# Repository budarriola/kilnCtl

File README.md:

# kilnCtl

> **WARNING: read the [Liability waiver and safety disclaimer](#liability-waiver-and-safety-disclaimer)
> before you build, flash, wire, or power anything from this repository.**
> This is an unfinished, experimental controller for an appliance that runs above
> 1000 °C on mains power. Even where it is believed to be stable, assume it **will**
> start a fire that burns your house down with everyone inside it.

A kiln controller: three KiCad boards, two independent firmwares, and the PC
tooling that drives both.

Heating is commanded by an ESP32-S3 through solid-state relays. A separate
RP2040 watches the same kiln and can cut power through a mechanical pilot relay
that is wired in series with the contactor coil. The two processors talk over an
opto-isolated UART, and the main processor is not allowed to heat unless the
safety processor is answering.

## Start here

**[ROADMAP.md](ROADMAP.md)** is the top-level plan across both processors. It
holds the milestone order and the cross-processor dependencies, and links to the
plan that owns each area. If you do not already know which document covers what
you are about to do, start there.

## Running the regression suite

```
python tools/regression_suite.py
```

One command, every automated gate this repo has, one pass/fail summary and a
non-zero exit on any failure (usable in CI or a pre-commit hook). It runs, in
order: `tools/run_all_checks.ps1` (the mechanical `check_*.ps1` guards, plus
the JS/browser harnesses and the headless-Chrome responsive sweep, which are
themselves wired into that script's discovery); then, in parallel, the KilnFW
and SaftyFW off-target host-test suites and the `tools/PcTools` pytest suite
(its live-bench tests self-skip with no board attached); then,
in parallel, the two target firmware *compiles* (KilnFW over ESP-IDF, SaftyFW
over pico-sdk -- no flashing, ever). One gate failing does not stop the
others; the final summary lists every gate's pass/fail and points at the full
log for anything that failed. See the script's own header comment for why
each stage is grouped and parallelized the way it is.

## Opening this repository

On a fresh clone, run **[`tools/setup.ps1`](tools/setup.ps1)** first — it
discovers where ESP-IDF, clangd and OpenOCD live on this machine and generates
the config files that cannot be committed. Full detail:
[docs/SETUP.md](docs/SETUP.md).

In VS Code, open **`kilnCtl.code-workspace`** rather than the `kilnCtl` folder.
The ESP-IDF extension treats a workspace folder as one project and needs a
`CMakeLists.txt` in it; the repository root does not have one. The workspace file
lists each firmware, `tools/PcTools` and `hardware` as folders in their own right,
and carries the shared tasks.

Shell commands in this repository are written to run from the root, so they carry
a path argument: `idf.py -C firmware/KilnFW build`,
`uv run --project tools/PcTools kilnctrl-gui`.

## Layout

```
hardware/   KiCad projects, shared library, datasheets, LTspice, sourcing
firmware/   KilnFW (ESP32-S3), SaftyFW (RP2040), CommonFW (shared)
tools/      PcTools - GUI and MCP server for both processors
docs/       System-level documents that span hardware and firmware
```

`mykicadMcp/` and `pdfMcp/` both moved under `tools/` 2026-08-28.
The rationale for the split, and what broke during it, is
[docs/REPO_LAYOUT.md](docs/REPO_LAYOUT.md).

## The three boards

| Board | What it is |
|---|---|
| `hardware/mainBoard` | ESP32-S3 controller, SSR drivers, current sense, isolated link, safety RP2040 |
| `hardware/ThermocoupleBoard` | 3-channel MAX31856 daughterboard |
| `hardware/SaftyThermocoupleBoard` | The safety processor's own thermocouple front end |

`Thermocouple.kicad_sch` appears in more than one project as a copy of the same
circuit, so a fix found in one usually applies to the others.

## The two firmwares

- **`firmware/KilnFW`** — ESP-IDF. Thermocouples, PID, profile execution, Wi-Fi
  provisioning, web UI. Partly built, partly verified on hardware; the honest
  ledger is [firmware/KilnFW/docs/PROJECT_STATUS.md](firmware/KilnFW/docs/PROJECT_STATUS.md).
- **`firmware/SaftyFW`** — pico-sdk and FreeRTOS SMP. Independent overheat and
  fault detection, owns the pilot relay. Planned in detail, **not yet built**.
- **`firmware/CommonFW`** — the link contract and its codecs, implemented once
  and linked by both. Also not yet built.

The safety processor's job is to catch faults, not to be sensitive: every trip
has to clear both a magnitude that correct operation cannot reach and a duration
a transient cannot sustain. That reasoning is
[firmware/SaftyFW/docs/SAFETY_MODEL.md](firmware/SaftyFW/docs/SAFETY_MODEL.md).

## Tooling

`tools/PcTools` is one GUI and one MCP server for both processors — serial to
the ESP, the isolated UART or SWD to the Pico, per-processor consoles and log
files. See [tools/PcTools/README.md](tools/PcTools/README.md) for what exists and
[tools/PcTools/TODO.md](tools/PcTools/TODO.md) for what is planned.

`mykicadMcp` is a separate submodule exposing KiCad inspection, sourcing and
autorouting over MCP.

## Bench setup

Programming, debug and console for the RP2040 all go through a Raspberry Pi
Debug Probe: SWD to the DEBUG pads, and the probe's UART bridge on GP16/GP17.
The Pico's own USB is deliberately not used. Wiring is
[firmware/SaftyFW/docs/HARDWARE.md](firmware/SaftyFW/docs/HARDWARE.md) §7b.

## Liability waiver and safety disclaimer

**This project is a work in progress. It is not finished, not certified, and not
safe.** Everything in this repository (schematics, PCB layouts, firmware for both
processors, PC tools, documentation, release images, and any advice in issues or
discussions) is an experimental, hobbyist development effort that is still
changing daily.

**Even where a part of it is believed to be stable, it is not.** Code that has
passed every test in this repository, every bench run, and every review can still
fail in the field. Treat every release, including those marked "stable", as a
pre-release prototype.

**Assume it will burn your house down with everyone inside.** A kiln is a
resistive heater that reaches well above 1000 °C, draws tens of amps from mains
power, and is often left unattended for many hours. A controller fault, a
firmware bug, a stuck or welded relay, a failed thermocouple, a wiring mistake, a
bad update, a power glitch, or a single misread value can leave the elements
energized with nothing to stop them. The likely result is a fire that destroys the
building and kills or seriously injures the people and animals inside it.
Electrocution, burns, toxic fumes, and damage to the kiln, its contents and
nearby property are also likely. Plan as if these outcomes will happen, not as if
they might.

**The safety processor does not make this safe.** The RP2040 safety processor, its
trip guards, the E-stop path, the pilot relay, and every other protective feature
described here are part of the same unfinished, unverified design. They have not
been independently evaluated and must not be relied on to prevent fire, injury or
death. This design does not replace a certified, independent over-temperature
cutoff, a correctly rated contactor, proper overcurrent protection, a
non-combustible installation, working smoke and fire detection, and a person
physically present and watching the kiln.

**No certification.** Nothing here has been tested, listed or approved by UL, CSA,
CE, TÜV, or any other safety or standards body, and nothing here complies with
any electrical, building or fire code. Installing it may break local law, void
your insurance, and void the kiln manufacturer's warranty. Mains wiring must be
done by a licensed electrician where your jurisdiction requires it.

**No warranty.** This project is provided "AS IS" and "AS AVAILABLE", without
warranty of any kind, express or implied. That includes, without limitation, any
warranty of merchantability, fitness for a particular purpose, safety, accuracy,
reliability, non-infringement, or that it will work at all.

**No liability.** To the fullest extent permitted by law, the authors,
contributors, copyright holders, and anyone who distributes this project are not
liable for any claim, damage, injury, death, loss of property, loss of data, loss
of income, or other loss of any kind, whether direct, indirect, incidental,
special, consequential, or punitive, and whether based on contract, tort
(including negligence), strict liability, or any other theory. This holds even if
they were told such loss was possible, and it applies to any use of this project,
any inability to use it, and any failure of it.

**You accept all risk.** By building, flashing, installing, operating, modifying,
or distributing anything from this repository, you agree that you do so entirely
at your own risk, that you are solely responsible for the safety of your
installation and of everyone and everything near it, and that you will indemnify
and hold harmless the authors and contributors against any claim arising from
your use. If you do not accept these terms, do not use this project.

**Not advice.** Nothing in this repository is professional, electrical,
engineering, or legal advice. If any part of this waiver cannot be enforced where
you live, the rest of it still applies.

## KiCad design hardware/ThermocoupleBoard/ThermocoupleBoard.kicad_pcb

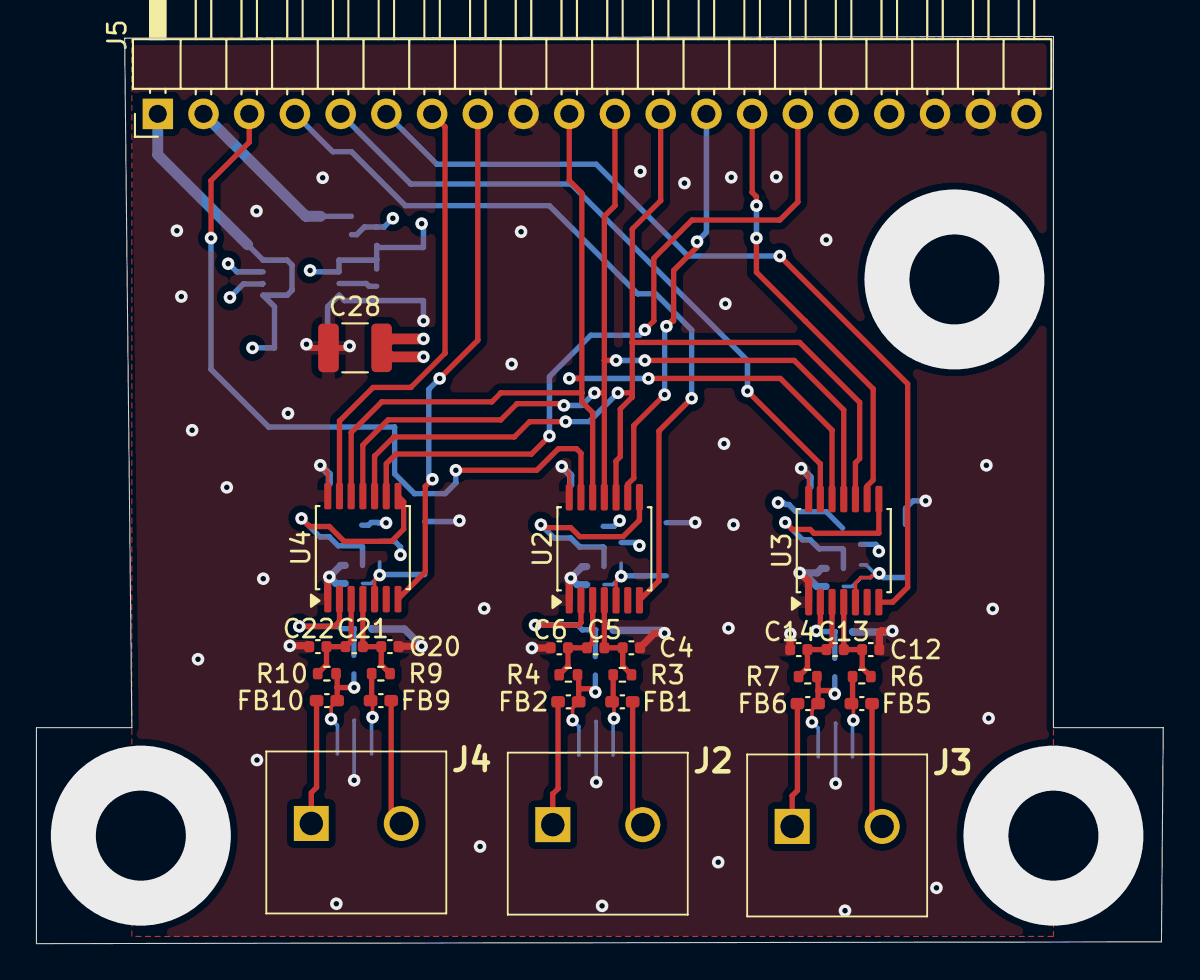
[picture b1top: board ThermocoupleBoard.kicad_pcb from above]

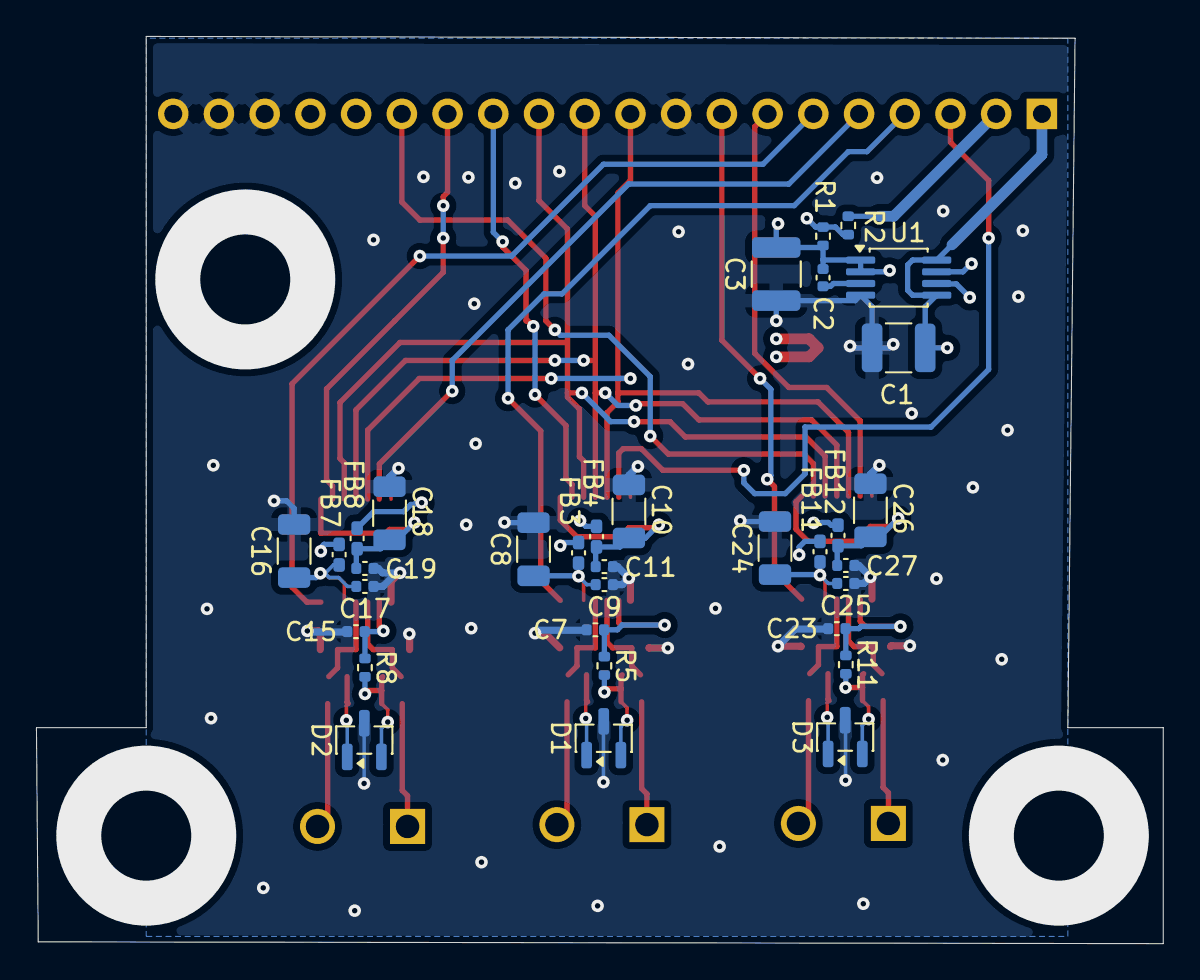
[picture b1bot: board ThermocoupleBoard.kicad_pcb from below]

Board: 4 copper layers, 62.6 x 50.4 mm, 62 parts (33 on the bottom side), 45 nets.

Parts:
C1, C3, C28: 47uF 16V; C_1210_3225Metric
C2, C4, C6, C7, C12, C14, C15, C20, C22, C23: 0.01uf; C_0402_1005Metric
C5, C9, C11, C13, C17, C19, C21, C25, C27: 0.1uf; C_0402_1005Metric
C8, C10, C16, C18, C24, C26: 2.2uF; C_1206_3216Metric
D1, D2, D3: NUP2105L; SOT-23
FB1, FB2, FB3, FB4, FB5, FB6, FB7, FB8, FB9, FB10, FB11, FB12: 1.8k; L_0402_1005Metric_Pad0.77x0.64mm_HandSolder
J2, J3, J4: 1935161
J5: Conn_01x20_Pin; PinHeader_1x20_P2.54mm_Horizontal
R1, R2: 0; R_0402_1005Metric
R3, R4, R5, R6, R7, R8, R9, R10, R11: 2.2k; R_0402_1005Metric
U1: LT1962-3.3; MSOP-8_3x3mm_P0.65mm
U2, U3, U4: MAX31856; TSSOP-14_4.4x5mm_P0.65mm

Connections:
3.3V_A: C2.1, C3.2, FB3.2, FB7.2, FB11.2, R1.2, U1.1 (OUT), U1.2 (SENSE)
3.3_D: C28.2, FB4.2, FB8.2, FB12.2, R1.1, R2.1
5V: C1.2, J5.1, U1.5 (~SHDN), U1.8 (IN)
/CLK: J5.12, U2.10 (SCK), U3.10 (SCK), U4.10 (SCK)
/CS0: J5.13, U2.9 (~CS)
/CS1: J5.14, U3.9 (~CS)
/CS2: J5.15, U4.9 (~CS)
/MISO: J5.11, U2.11 (SDO), U3.11 (SDO), U4.11 (SDO)
/MOSI: J5.10, U2.12 (SDI), U3.12 (SDI), U4.12 (SDI)
/thermoDrdy_0: J5.4, U2.7 (~DRDY)
/thermoDrdy_1: J5.6, U3.7 (~DRDY)
/thermoDrdy_2: J5.8, U4.7 (~DRDY)
/thermoFault_0: J5.3, U2.13 (~FAULT)
/thermoFault_1: J5.5, U3.13 (~FAULT)
/thermoFault_2: J5.7, U4.13 (~FAULT)
GND: C1.1, C3.1, C4.1, C6.2, C7.2, C8.2, C9.2, C10.2, C11.2, C12.1, C14.2, C15.2, C16.2, C17.2, C18.2, C19.2, C20.1, C22.2, C23.2, C24.2, C25.2, C26.2, C27.2, C28.1, D1.3 (A), D2.3 (A), D3.3 (A), J5.9, J5.18, J5.19, J5.20, U1.4 (GND), U2.1 (AGND), U2.14 (DGND), U3.1 (AGND), U3.14 (DGND), U4.1 (AGND), U4.14 (DGND)
unnamed: D1.1 (K), FB1.2, R3.2
unnamed: D1.2 (K), FB2.2, R4.2, R5.2
unnamed: D2.1 (K), FB5.2, R6.2
unnamed: D2.2 (K), FB6.2, R7.2, R8.2
unnamed: D3.1 (K), FB9.2, R9.2
unnamed: D3.2 (K), FB10.2, R10.2, R11.2
unnamed: FB1.1, J2.2
unnamed: FB2.1, J2.1
unnamed: FB5.1, J3.2
unnamed: FB6.1, J3.1
unnamed: FB9.1, J4.2
unnamed: FB10.1, J4.1
unnamed: J5.2, R2.2
unnamed: C2.2, U1.3 (BYP)
unnamed: C8.1, C9.1, FB3.1, U2.5 (AVDD)
unnamed: C7.1, R5.1, U2.2 (BIAS)
unnamed: C10.1, C11.1, FB4.1, U2.8 (DVDD)
unnamed: C4.2, C5.1, R3.1, U2.4 (T+)
unnamed: C5.2, C6.1, R4.1, U2.3 (T-)
unnamed: C16.1, C17.1, FB7.1, U3.5 (AVDD)
unnamed: C15.1, R8.1, U3.2 (BIAS)
unnamed: C18.1, C19.1, FB8.1, U3.8 (DVDD)
unnamed: C12.2, C13.1, R6.1, U3.4 (T+)
unnamed: C13.2, C14.1, R7.1, U3.3 (T-)
unnamed: C24.1, C25.1, FB11.1, U4.5 (AVDD)
unnamed: C23.1, R11.1, U4.2 (BIAS)
unnamed: C26.1, C27.1, FB12.1, U4.8 (DVDD)
unnamed: C20.2, C21.1, R9.1, U4.4 (T+)
unnamed: C21.2, C22.1, R10.1, U4.3 (T-)

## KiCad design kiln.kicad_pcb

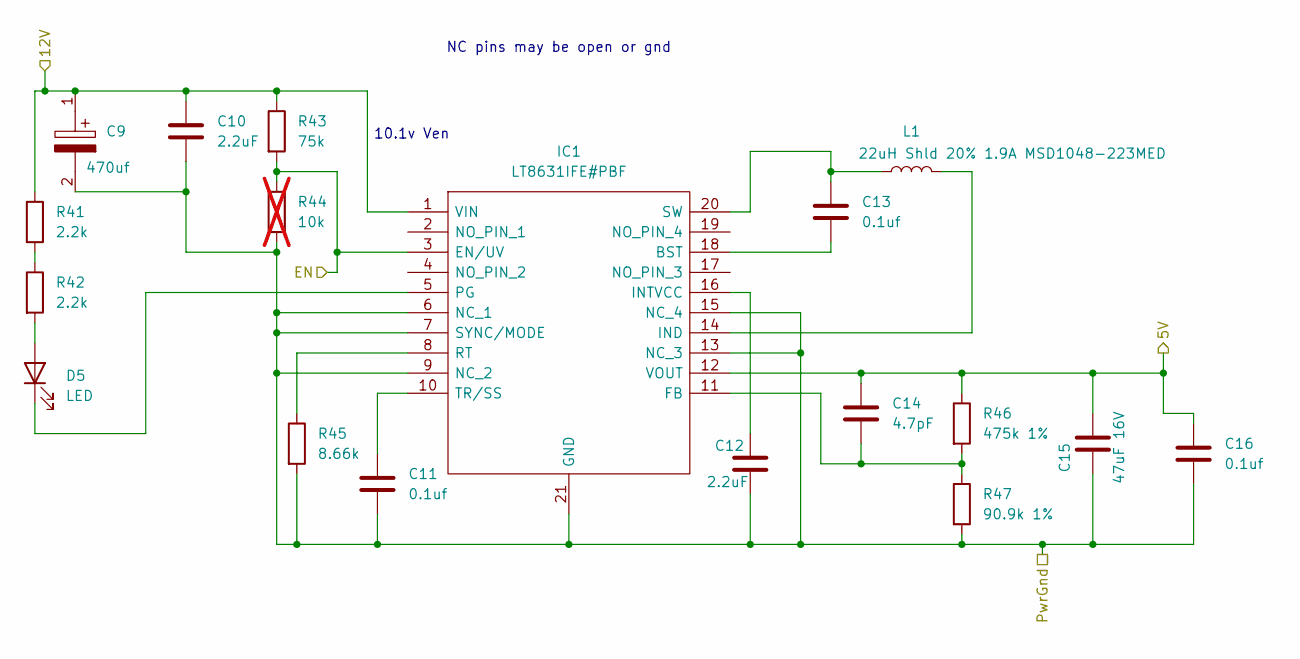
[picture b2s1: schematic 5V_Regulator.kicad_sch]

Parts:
C9: 470uf; CAPAE1360X1450N; Mouser Part Number 647-UCM1H471MNJ1MS
C10, C12: 2.2uF; C_1206_3216Metric
C11, C13, C16: 0.1uf; C_0402_1005Metric
C14: 4.7pF; C_0402_1005Metric
C15: 47uF 16V; C_1210_3225Metric
D5: LED; LED_0402_1005Metric
IC1: LT8631IFE#PBF; SOP65P640X120-21N; Mouser Part Number 584-LT8631IFE#PBF
L1: 22uH Shld 20% 1.9A MSD1048-223MED; L_Bourns_SRP1038C_10.0x10.0mm
R41, R42: 2.2k; R_0805_2012Metric
R43: 75k; R_0402_1005Metric
R44: 10k; R_0402_1005Metric; not fitted
R45: 8.66k; R_0402_1005Metric
R46: 475k 1%; R_0402_1005Metric
R47: 90.9k 1%; R_0402_1005Metric

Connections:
5V_Main: C14.1, C15.2, C16.1, IC1.12 (VOUT), R46.1; also elsewhere on the board
12V_Main: C9.1, C10.1, IC1.1 (VIN), R41.1, R43.1; also elsewhere on the board
/MainRegulator/PGoodMain: IC1.3 (EN/UV), R43.2, R44.1; also elsewhere on the board
GND_Main: C9.2, C10.2, C11.2, C12.2, C15.1, C16.2, IC1.6 (NC_1), IC1.7 (SYNC/MODE), IC1.9 (NC_2), IC1.13 (NC_3), IC1.15 (NC_4), IC1.21 (GND), R44.2, R45.2, R47.2; also elsewhere on the board
unnamed: D5.2 (A), R42.2
unnamed: D5.1 (K), IC1.5 (PG)
unnamed: C13.2, IC1.18 (BST)
unnamed: C14.2, IC1.11 (FB), R46.2, R47.1
unnamed: IC1.14 (IND), L1.2
unnamed: C12.1, IC1.16 (INTVCC)
unnamed: IC1.8 (RT), R45.1
unnamed: C13.1, IC1.20 (SW), L1.1
unnamed: C11.1, IC1.10 (TR/SS)
unnamed: R41.2, R42.1

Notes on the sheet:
10.1v Ven
NC pins may be open or gnd

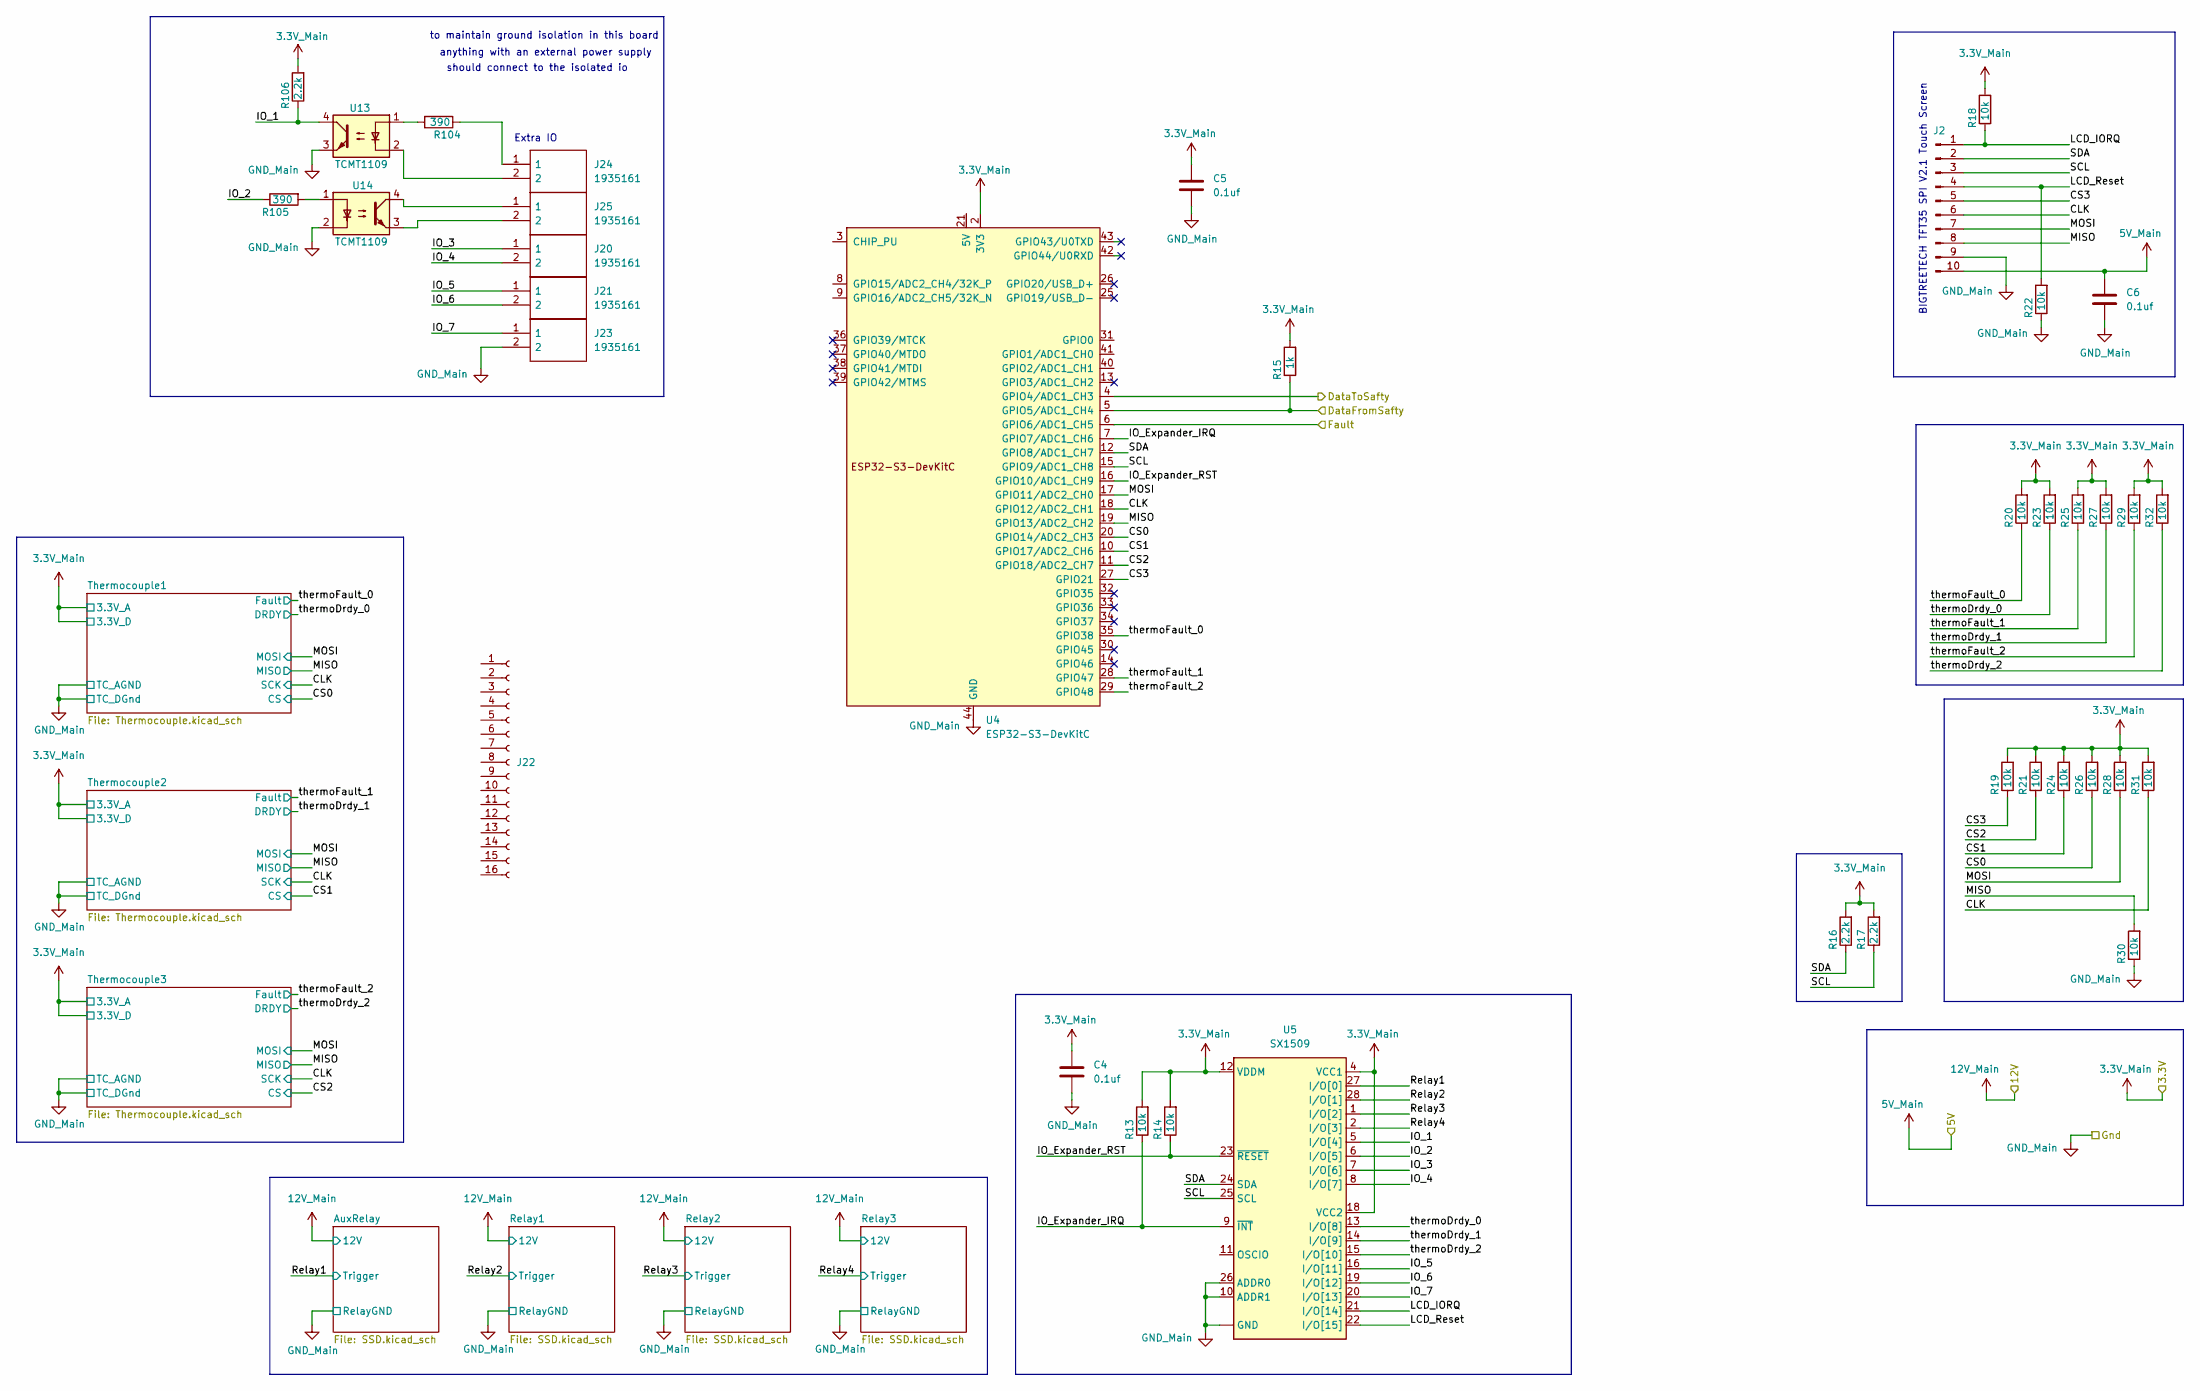
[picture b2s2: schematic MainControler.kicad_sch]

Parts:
C4, C5, C6: 0.1uf; C_0402_1005Metric
J2: Conn_01x10_Pin; JST_XH_B10B-XH-AM_1x10_P2.50mm_Vertical
J20, J21, J23, J24, J25: 1935161; Mouser Part Number 651-1935161
J22: Conn_01x16_Socket; PinSocket_1x16_P2.54mm_Horizontal
R13, R14, R18, R19, R20, R21, R22, R23, R24, R25, R26, R27, R28, R29, R30, R31, R32: 10k; R_0402_1005Metric
R15: 1k; R_0402_1005Metric
R16, R17, R106: 2.2k; R_0402_1005Metric
R104, R105: 390; R_0402_1005Metric
U4: ESP32-S3-DevKitC
U5: SX1509; QFN-28-1EP_4x4mm_P0.4mm_EP2.6x2.6mm; Manufacturer_Part_Number SX1509BIULTRT
U13, U14: TCMT1109; SOP-4_4.4x2.6mm_P1.27mm

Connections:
3.3V_Main: C4.1, C5.1, R13.2, R14.2, R15.2, R16.2, R17.2, R18.2, R19.2, R20.2, R21.2, R23.2, R24.2, R25.2, R26.2, R27.2, R28.2, R29.2, R31.2, R32.2, R106.2, U4.1 (3V3), U4.2 (3V3), U5.4 (VCC1), U5.12 (VDDM), U5.18 (VCC2); also elsewhere on the board
5V_Main: C6.1, J2.10; also elsewhere on the board
/MainControler/CLK: J2.6, R31.1, U4.18 (GPIO12/ADC2_CH1); also elsewhere on the board
/MainControler/CS0: R26.1, U4.20 (GPIO14/ADC2_CH3); also elsewhere on the board
/MainControler/CS1: R24.1, U4.10 (GPIO17/ADC2_CH6); also elsewhere on the board
/MainControler/CS2: R21.1, U4.11 (GPIO18/ADC2_CH7); also elsewhere on the board
/MainControler/CS3: J2.5, R19.1, U4.27 (GPIO21)
/MainControler/DataFromSafty: R15.1, U4.5 (GPIO5/ADC1_CH4); also elsewhere on the board
/MainControler/DataToSafty: U4.4 (GPIO4/ADC1_CH3); also elsewhere on the board
/MainControler/Fault: U4.6 (GPIO6/ADC1_CH5); also elsewhere on the board
/MainControler/IO_1: R106.1, U5.5 (I/O[4]), U13.4
/MainControler/IO_2: R105.1, U5.6 (I/O[5])
/MainControler/IO_3: J20.1, U5.7 (I/O[6])
/MainControler/IO_4: J20.2, U5.8 (I/O[7])
/MainControler/IO_5: J21.1, U5.16 (I/O[11])
/MainControler/IO_6: J21.2, U5.19 (I/O[12])
/MainControler/IO_7: J23.1, U5.20 (I/O[13])
/MainControler/IO_Expander_IRQ: R13.1, U4.7 (GPIO7/ADC1_CH6), U5.9 (~INT)
/MainControler/IO_Expander_RST: R14.1, U4.16 (GPIO10/ADC1_CH9), U5.23 (~RESET)
/MainControler/LCD_IORQ: J2.1, R18.1, U5.21 (I/O[14])
/MainControler/LCD_Reset: J2.4, R22.2, U5.22 (I/O[15])
/MainControler/MISO: J2.8, R30.2, U4.19 (GPIO13/ADC2_CH2); also elsewhere on the board
/MainControler/MOSI: J2.7, R28.1, U4.17 (GPIO11/ADC2_CH0); also elsewhere on the board
/MainControler/Relay1: U5.27 (I/O[0]); also elsewhere on the board
/MainControler/Relay2: U5.28 (I/O[1]); also elsewhere on the board
/MainControler/Relay3: U5.1 (I/O[2]); also elsewhere on the board
/MainControler/Relay4: U5.2 (I/O[3]); also elsewhere on the board
/MainControler/SCL: J2.3, R17.1, U4.15 (GPIO9/ADC1_CH8), U5.25 (SCL)
/MainControler/SDA: J2.2, R16.1, U4.12 (GPIO8/ADC1_CH7), U5.24 (SDA)
/MainControler/thermoDrdy_0: R23.1, U5.13 (I/O[8]); also elsewhere on the board
/MainControler/thermoDrdy_1: R27.1, U5.14 (I/O[9]); also elsewhere on the board
/MainControler/thermoDrdy_2: R32.1, U5.15 (I/O[10]); also elsewhere on the board
/MainControler/thermoFault_0: R20.1, U4.35 (GPIO38); also elsewhere on the board
/MainControler/thermoFault_1: R25.1, U4.28 (GPIO47); also elsewhere on the board
/MainControler/thermoFault_2: R29.1, U4.29 (GPIO48); also elsewhere on the board
GND_Main: C4.2, C5.2, C6.2, J2.9, J23.2, R22.1, R30.1, U4.22 (GND), U4.23 (GND), U4.24 (GND), U4.44 (GND), U5.3 (GND), U5.10 (ADDR1), U5.17 (GND), U5.26 (ADDR0), U5.29 (GND), U13.3, U14.2; also elsewhere on the board
unnamed: J24.1, R104.1
unnamed: J24.2, U13.2
unnamed: J25.1, U14.4
unnamed: J25.2, U14.3
unnamed: R104.2, U13.1
unnamed: R105.2, U14.1

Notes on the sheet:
BIGTREETECH TFT35 SPI V2.1 Touch Screen
anything with an external power supply
to maintain ground isolation in this board
should connect to the isolated io
Extra IO

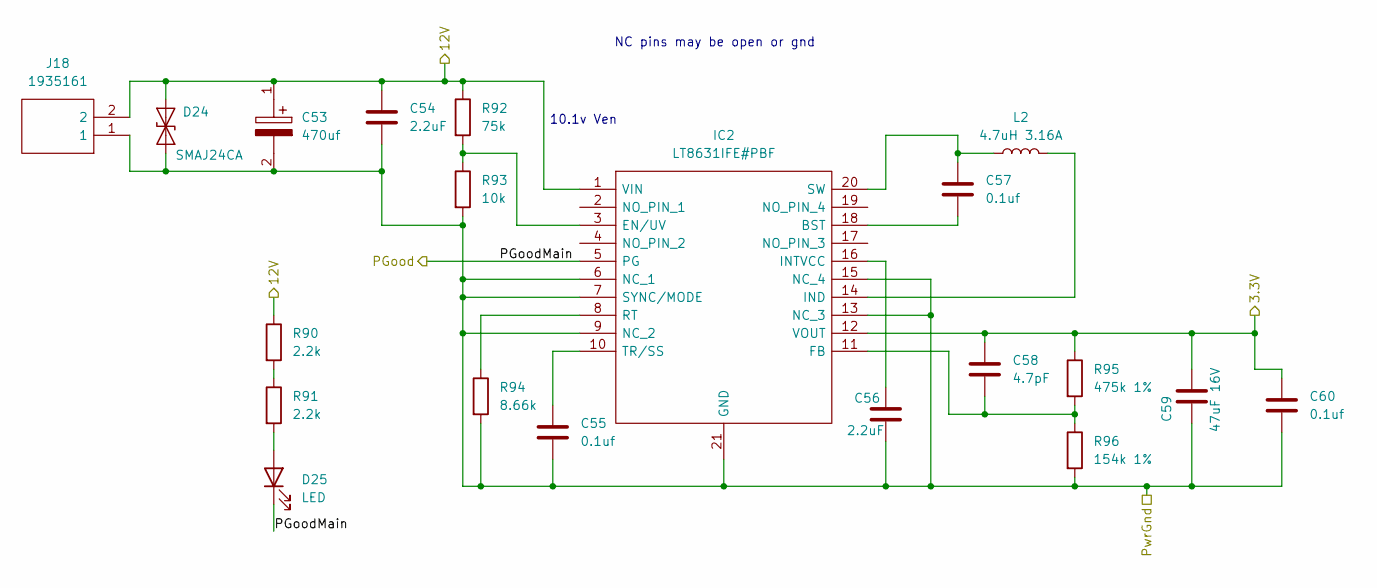
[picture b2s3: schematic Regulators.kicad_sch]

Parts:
C53: 470uf; CAPAE1360X1450N; Mouser Part Number 647-UCM1H471MNJ1MS
C54, C56: 2.2uF; C_1206_3216Metric
C55, C57, C60: 0.1uf; C_0402_1005Metric
C58: 4.7pF; C_0402_1005Metric
C59: 47uF 16V; C_1210_3225Metric
D24: SMAJ24CA; D_SMA
D25: LED; LED_0402_1005Metric
IC2: LT8631IFE#PBF; SOP65P640X120-21N; Mouser Part Number 584-LT8631IFE#PBF
J18: 1935161; Mouser Part Number 651-1935161
L2: 4.7uH 3.16A; L_7.3x7.3_H4.5
R90, R91: 2.2k; R_0805_2012Metric
R92: 75k; R_0402_1005Metric
R93: 10k; R_0402_1005Metric
R94: 8.66k; R_0402_1005Metric
R95: 475k 1%; R_0402_1005Metric
R96: 154k 1%; R_0402_1005Metric

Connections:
3.3V_Main: C58.1, C59.2, C60.1, IC2.12 (VOUT), R95.1; also elsewhere on the board
12V_Main: C53.1, C54.1, D24.2 (A2), IC2.1 (VIN), J18.2, R90.1, R92.1; also elsewhere on the board
/MainRegulator/PGoodMain: D25.1 (K), IC2.5 (PG); also elsewhere on the board
GND_Main: C53.2, C54.2, C55.2, C56.2, C59.1, C60.2, D24.1 (A1), IC2.6 (NC_1), IC2.7 (SYNC/MODE), IC2.9 (NC_2), IC2.13 (NC_3), IC2.15 (NC_4), IC2.21 (GND), J18.1, R93.2, R94.2, R96.2; also elsewhere on the board
unnamed: D25.2 (A), R91.2
unnamed: C57.2, IC2.18 (BST)
unnamed: IC2.3 (EN/UV), R92.2, R93.1
unnamed: C58.2, IC2.11 (FB), R95.2, R96.1
unnamed: IC2.14 (IND), L2.2
unnamed: C56.1, IC2.16 (INTVCC)
unnamed: IC2.8 (RT), R94.1
unnamed: C57.1, IC2.20 (SW), L2.1
unnamed: C55.1, IC2.10 (TR/SS)
unnamed: R90.2, R91.1

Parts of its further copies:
C61: 470uf; CAPAE1360X1450N; Mouser Part Number 647-UCM1H471MNJ1MS
C62, C64: 2.2uF; C_1206_3216Metric
C63, C65, C68: 0.1uf; C_0402_1005Metric
C66: 4.7pF; C_0402_1005Metric
C67: 47uF 16V; C_1210_3225Metric
D26: SMAJ24CA; D_SMA
D27: LED; LED_0402_1005Metric
IC3: LT8631IFE#PBF; SOP65P640X120-21N; Mouser Part Number 584-LT8631IFE#PBF
J19: 1935161; Mouser Part Number 651-1935161
L3: 4.7uH 3.16A; L_7.3x7.3_H4.5
R97, R98: 2.2k; R_0805_2012Metric
R99: 75k; R_0402_1005Metric
R100: 10k; R_0402_1005Metric
R101: 8.66k; R_0402_1005Metric
R102: 475k 1%; R_0402_1005Metric
R103: 154k 1%; R_0402_1005Metric

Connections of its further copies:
3.3v_Safty: C66.1, C67.2, C68.1, IC3.12 (VOUT), R102.1; also elsewhere on the board
12v_Safty: C61.1, C62.1, D26.2 (A2), IC3.1 (VIN), J19.2, R97.1, R99.1; also elsewhere on the board
/SaftyRegulator/PGoodMain: D27.1 (K), IC3.5 (PG)
GND_Safty: C61.2, C62.2, C63.2, C64.2, C67.1, C68.2, D26.1 (A1), IC3.6 (NC_1), IC3.7 (SYNC/MODE), IC3.9 (NC_2), IC3.13 (NC_3), IC3.15 (NC_4), IC3.21 (GND), J19.1, R100.2, R101.2, R103.2; also elsewhere on the board
unnamed: D27.2 (A), R98.2
unnamed: C65.2, IC3.18 (BST)
unnamed: IC3.3 (EN/UV), R99.2, R100.1
unnamed: C66.2, IC3.11 (FB), R102.2, R103.1
unnamed: IC3.14 (IND), L3.2
unnamed: C64.1, IC3.16 (INTVCC)
unnamed: IC3.8 (RT), R101.1
unnamed: C65.1, IC3.20 (SW), L3.1
unnamed: C63.1, IC3.10 (TR/SS)
unnamed: R97.2, R98.1

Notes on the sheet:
NC pins may be open or gnd
10.1v Ven

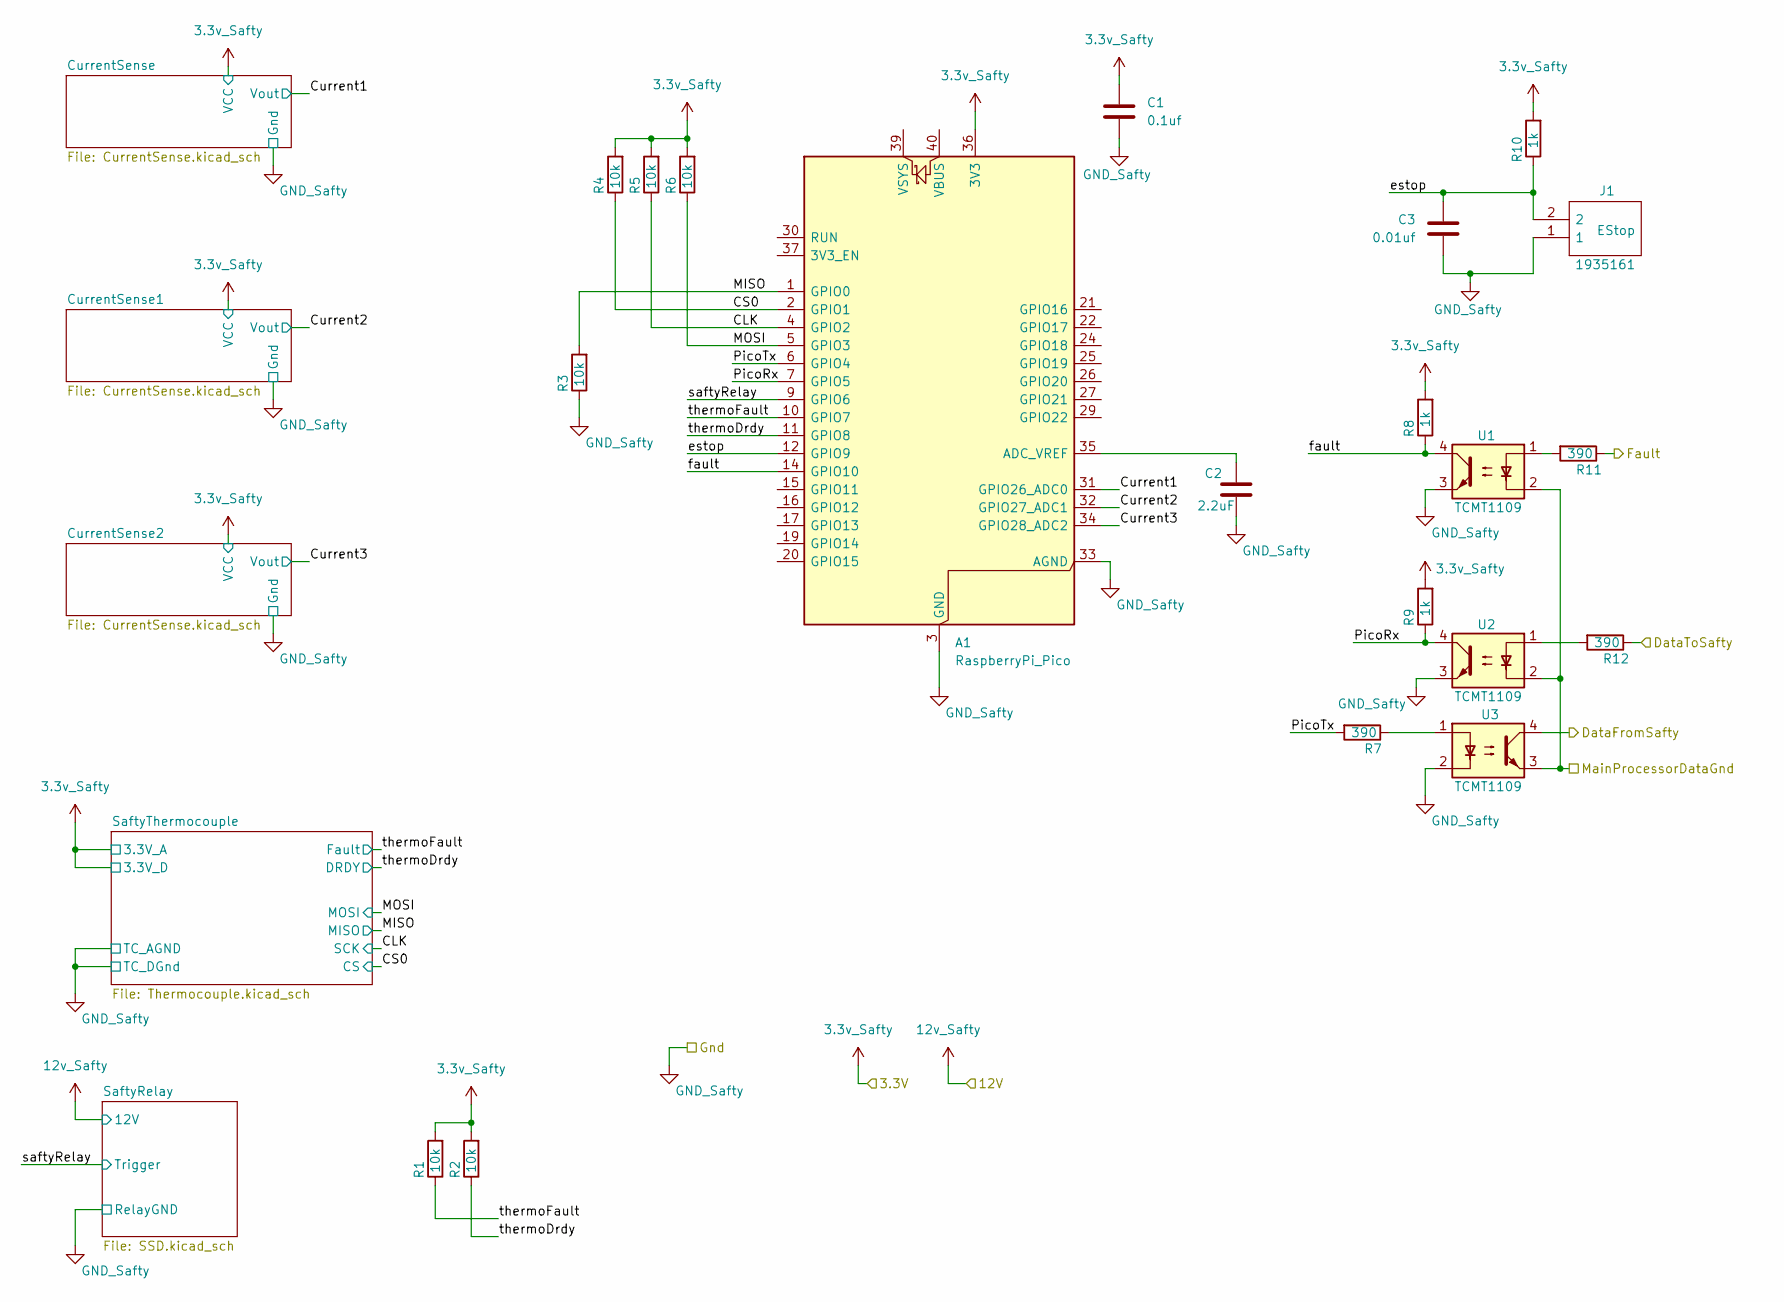
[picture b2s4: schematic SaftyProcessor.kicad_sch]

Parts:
A1: RaspberryPi_Pico; RaspberryPi_Pico_Common_Unspecified
C1: 0.1uf; C_0402_1005Metric
C2: 2.2uF; C_1206_3216Metric
C3: 0.01uf; C_0402_1005Metric
J1: 1935161; Mouser Part Number 651-1935161
R1, R2, R3, R4, R5, R6: 10k; R_0402_1005Metric
R7, R11, R12: 390; R_0402_1005Metric
R8, R9, R10: 1k; R_0402_1005Metric
U1, U2, U3: TCMT1109; SOP-4_4.4x2.6mm_P1.27mm

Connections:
3.3v_Safty: A1.36 (3V3), C1.1, R1.2, R2.2, R4.2, R5.2, R6.2, R8.2, R9.2, R10.2; also elsewhere on the board
/MainControler/DataFromSafty: R12.1; also elsewhere on the board
/MainControler/DataToSafty: U3.4; also elsewhere on the board
/MainControler/Fault: R11.1; also elsewhere on the board
/SaftyProcessor/CLK: A1.4 (GPIO2), R5.1; also elsewhere on the board
/SaftyProcessor/CS0: A1.2 (GPIO1), R4.1; also elsewhere on the board
/SaftyProcessor/Current1: A1.31 (GPIO26_ADC0); also elsewhere on the board
/SaftyProcessor/Current2: A1.32 (GPIO27_ADC1); also elsewhere on the board
/SaftyProcessor/Current3: A1.34 (GPIO28_ADC2); also elsewhere on the board
/SaftyProcessor/MISO: A1.1 (GPIO0), R3.2; also elsewhere on the board
/SaftyProcessor/MOSI: A1.5 (GPIO3), R6.1; also elsewhere on the board
/SaftyProcessor/PicoRx: A1.7 (GPIO5), R9.1, U2.4
/SaftyProcessor/PicoTx: A1.6 (GPIO4), R7.2
/SaftyProcessor/estop: A1.12 (GPIO9), C3.1, J1.2, R10.1
/SaftyProcessor/fault: A1.14 (GPIO10), R8.1, U1.4
/SaftyProcessor/saftyRelay: A1.9 (GPIO6); also elsewhere on the board
/SaftyProcessor/thermoDrdy: A1.11 (GPIO8), R2.1; also elsewhere on the board
/SaftyProcessor/thermoFault: A1.10 (GPIO7), R1.1; also elsewhere on the board
GND_Main: U1.2, U2.2, U3.3; also elsewhere on the board
GND_Safty: A1.3 (GND), A1.8 (GND), A1.13 (GND), A1.18 (GND), A1.23 (GND), A1.28 (GND), A1.33 (AGND), A1.38 (GND), C1.2, C2.2, C3.2, J1.1, R3.1, U1.3, U2.3, U3.2; also elsewhere on the board
unnamed: A1.35 (ADC_VREF), C2.1
unnamed: R7.1, U3.1
unnamed: R11.2, U1.1
unnamed: R12.2, U2.1

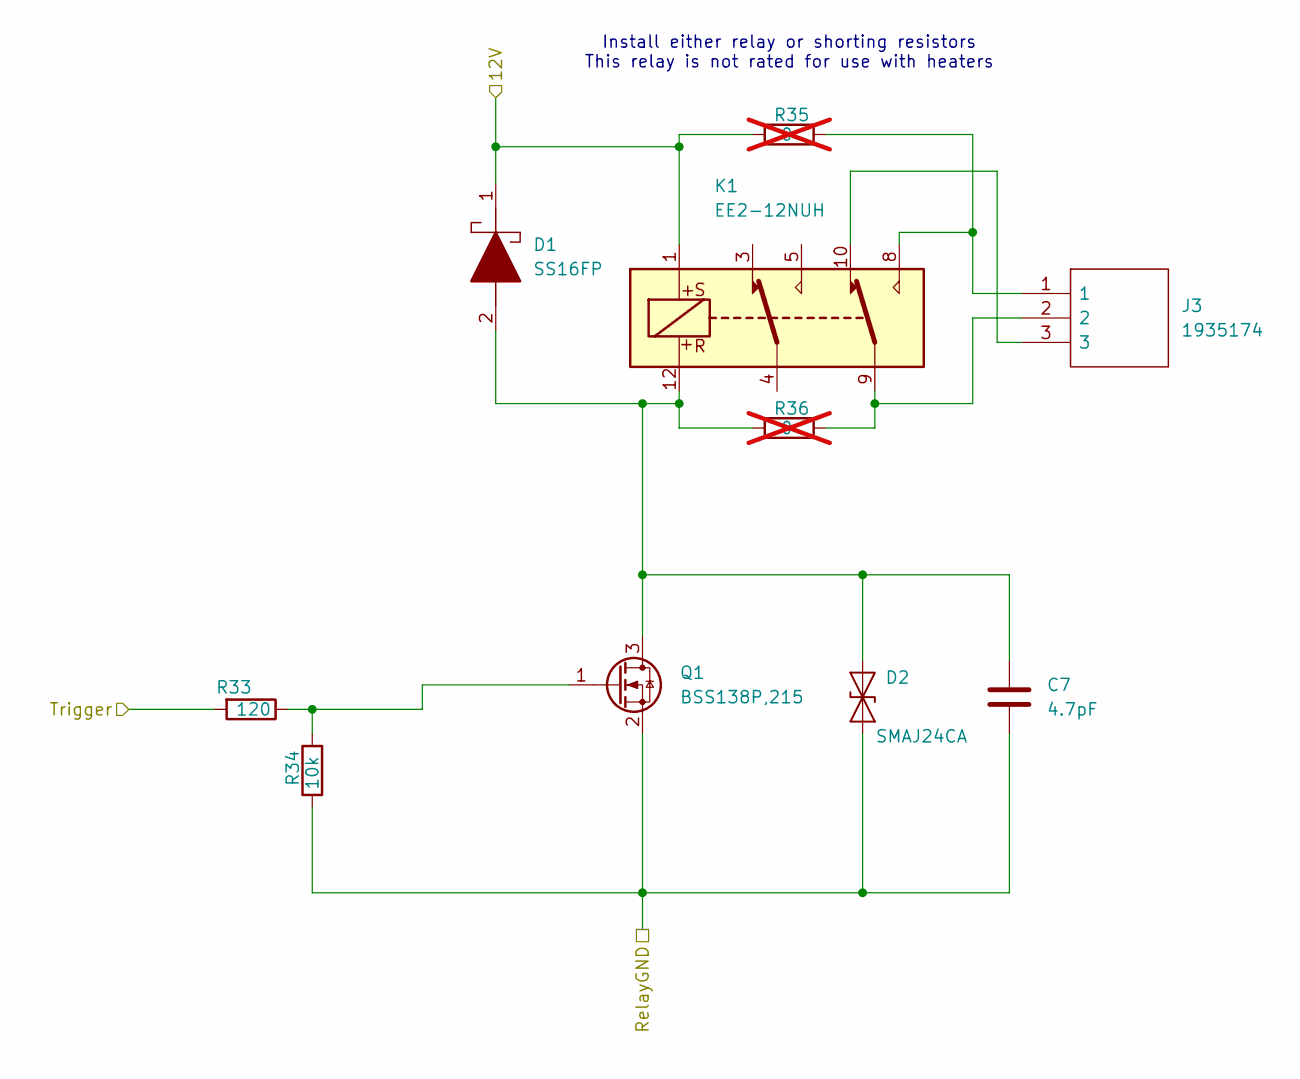
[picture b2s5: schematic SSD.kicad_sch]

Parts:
C7: 4.7pF; C_0402_1005Metric
D1: SS16FP; SS12FP; Mouser Part Number 512-SS16FP
D2: SMAJ24CA; D_SMA
J3: 1935174; Mouser Part Number 651-1935174
K1: EE2-12NUH; Relay_DPDT_Kemet_EE2_NUH
Q1: BSS138P,215; SOT-23
R33: 120; R_0402_1005Metric
R34: 10k; R_0402_1005Metric
R35, R36: 0; R_1206_3216Metric; not fitted

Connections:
12V_Main: D1.1, K1.1, R35.1; also elsewhere on the board
/MainControler/Relay2: R33.2; also elsewhere on the board
GND_Main: C7.2, D2.1 (A1), Q1.2 (S), R34.1; also elsewhere on the board
unnamed: C7.1, D1.2, D2.2 (A2), K1.12, Q1.3 (D), R36.1
unnamed: J3.1, K1.8, R35.2
unnamed: J3.2, K1.9, R36.2
unnamed: J3.3, K1.10
unnamed: Q1.1 (G), R33.1, R34.2

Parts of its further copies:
C8, C35, C42, C43: 4.7pF; C_0402_1005Metric
D3, D6, D8, D10: SS16FP; SS12FP; Mouser Part Number 512-SS16FP
D4, D7, D9, D11: SMAJ24CA; D_SMA
J4, J8, J10, J11: 1935174; Mouser Part Number 651-1935174
K2, K3, K4, K5: EE2-12NUH; Relay_DPDT_Kemet_EE2_NUH
Q2, Q3, Q4, Q5: BSS138P,215; SOT-23
R37, R57, R64, R68: 120; R_0402_1005Metric
R38, R58, R65, R69: 10k; R_0402_1005Metric
R39, R40, R59, R60, R66, R67, R70, R71: 0; R_1206_3216Metric; not fitted

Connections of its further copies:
12V_Main: D3.1, D6.1, D10.1, K2.1, K3.1, K5.1, R39.1, R59.1, R70.1; also elsewhere on the board
12v_Safty: D8.1, K4.1, R66.1; also elsewhere on the board
/MainControler/Relay1: R57.2; also elsewhere on the board
/MainControler/Relay3: R37.2; also elsewhere on the board
/MainControler/Relay4: R68.2; also elsewhere on the board
/SaftyProcessor/saftyRelay: R64.2; also elsewhere on the board
GND_Main: C8.2, C35.2, C43.2, D4.1 (A1), D7.1 (A1), D11.1 (A1), Q2.2 (S), Q3.2 (S), Q5.2 (S), R38.1, R58.1, R69.1; also elsewhere on the board
GND_Safty: C42.2, D9.1 (A1), Q4.2 (S), R65.1; also elsewhere on the board
unnamed: C8.1, D3.2, D4.2 (A2), K2.12, Q2.3 (D), R40.1
unnamed: C35.1, D6.2, D7.2 (A2), K3.12, Q3.3 (D), R60.1
unnamed: C42.1, D8.2, D9.2 (A2), K4.12, Q4.3 (D), R67.1
unnamed: C43.1, D10.2, D11.2 (A2), K5.12, Q5.3 (D), R71.1
unnamed: J4.1, K2.8, R39.2
unnamed: J4.2, K2.9, R40.2
unnamed: J4.3, K2.10
unnamed: J8.1, K3.8, R59.2
unnamed: J8.2, K3.9, R60.2
unnamed: J8.3, K3.10
unnamed: J10.1, K4.8, R66.2
unnamed: J10.2, K4.9, R67.2
unnamed: J10.3, K4.10
unnamed: J11.1, K5.8, R70.2
unnamed: J11.2, K5.9, R71.2
unnamed: J11.3, K5.10
unnamed: Q2.1 (G), R37.1, R38.2
unnamed: Q3.1 (G), R57.1, R58.2
unnamed: Q4.1 (G), R64.1, R65.2
unnamed: Q5.1 (G), R68.1, R69.2

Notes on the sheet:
Install either relay or shorting resistors This relay is not rated for use with heaters
